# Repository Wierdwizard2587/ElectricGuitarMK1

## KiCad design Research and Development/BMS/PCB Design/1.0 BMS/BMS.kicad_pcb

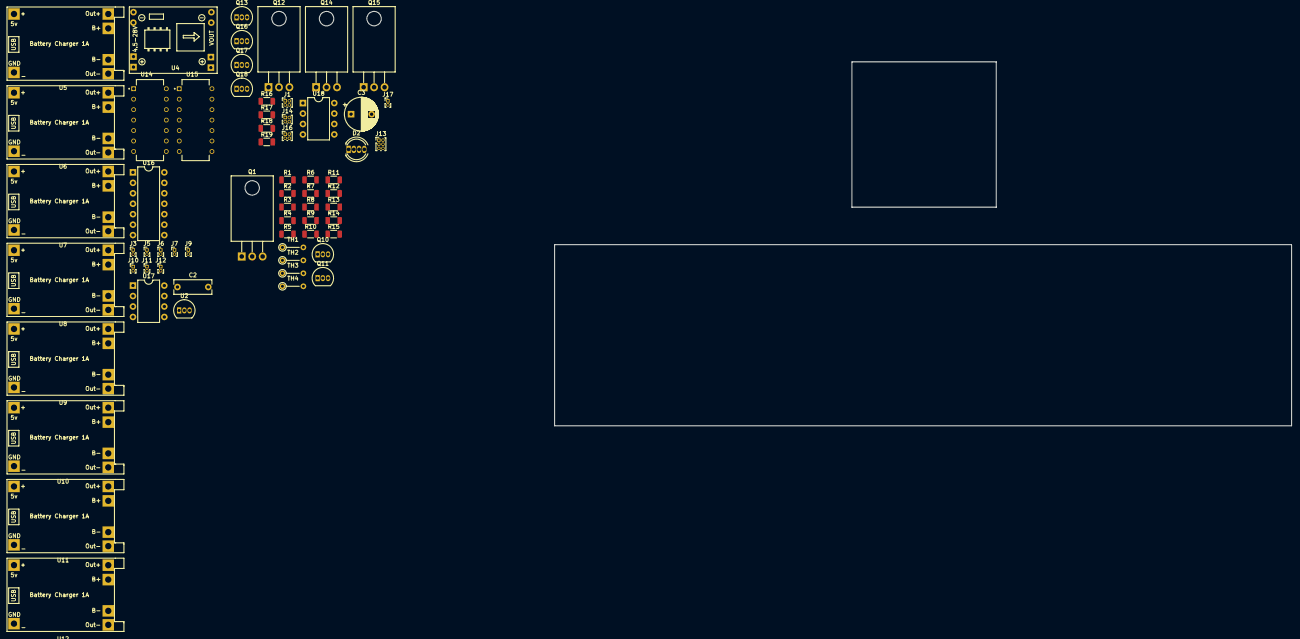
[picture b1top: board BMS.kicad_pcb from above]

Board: 2 copper layers, 179.0 x 88.4 mm, 64 parts (0 on the bottom side), 63 nets, no tracks yet.

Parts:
C2: 2nf; C_Rect_L9.0mm_W3.3mm_P7.50mm_MKT
C3: 220uf; CP_Radial_D8.0mm_P5.00mm
D2: LED_KGRB; LED_D5.0mm-4_RGB
J1, J14, J16: Conn_01x04_Pin; PinHeader_2x02_P1.00mm_Vertical
J3: Batt 1 Conn; PinHeader_1x02_P1.00mm_Vertical
J5: Batt 2 Conn; PinHeader_1x02_P1.00mm_Vertical
J6: Batt 3 Conn; PinHeader_1x02_P1.00mm_Vertical
J7: Batt 4 Conn; PinHeader_1x02_P1.00mm_Vertical
J9: Batt 5 Conn; PinHeader_1x02_P1.00mm_Vertical
J10: Batt 6 Conn; PinHeader_1x02_P1.00mm_Vertical
J11: Batt 7 Conn; PinHeader_1x02_P1.00mm_Vertical
J12: Batt 8 Conn; PinHeader_1x02_P1.00mm_Vertical
J13: Conn_01x06_Pin; PinHeader_2x03_P1.00mm_Vertical
J17: Moment ON B; PinHeader_1x02_P1.00mm_Vertical
Q1, Q12, Q14, Q15: IRL540; TO-220-3_Horizontal_TabDown
Q10, Q11, Q13, Q17, Q18: PN2222A; TO-92_Inline
Q16: ZVP2106A; TO-92_Inline
R1, R2, R3, R4, R5, R7, R11, R16: 10K; R_1206_3216Metric
R6, R8, R12, R13, R14, R15: R; R_1206_3216Metric
R9: 30K; R_1206_3216Metric
R10: 7.5K; R_1206_3216Metric
R17: 150R; R_1206_3216Metric
R18: 90R; R_1206_3216Metric
R19: 100R; R_1206_3216Metric
TH1, TH2, TH3, TH4: Thermistor_NTC; R_Axial_DIN0204_L3.6mm_D1.6mm_P5.08mm_Vertical
U2: 78L05; TO-92_Inline
U4: MP1584 Module; SRT_MPT1584EN_Module
U5, U6, U7, U8, U9, U10, U11, U12: TP4056 Charging Module; TP4056-18650
U14, U15: LM339; lm339n THT
U16: 74HC02; DIP-14_W7.62mm
U17: LM393; DIP-8_W7.62mm
U18: LMC555xN; DIP-8_W7.62mm

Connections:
BMS VCC 5V+: Q10.3 (C), R6.2, R8.2, R12.2, R16.2, TH1.2, TH2.2, TH3.2, TH4.2, U2.1 (VO), U14.3 (V+), U15.3 (V+), U16.14 (VCC), U17.8 (V+), U18.4 (R), U18.8 (VCC)
Batt Cuttoff Logic: Q1.1 (G), U17.1
Batt V: J1.2, J13.2, R9.1, R10.2, U17.3 (+)
Charge VCC: Q14.3 (S), U5.1 (IN+), U6.1 (IN+), U7.1 (IN+), U8.1 (IN+), U9.1 (IN+), U10.1 (IN+), U11.1 (IN+), U12.1 (IN+)
Charger Digital Signal: J13.4, Q12.1 (G), Q13.2 (B)
Charger In 5v+: J13.6, Q14.2 (D)
GND: C2.1, C3.2, D2.1 (K), J1.3, J13.3, J17.2, R1.1, R2.1, R3.1, R4.1, R5.1, R7.1, R10.1, R11.1, R15.2, U2.2 (GND), U4.1 (IN+), U4.4 (OUT-), U5.2 (IN-), U6.2 (IN-), U7.2 (IN-), U8.2 (IN-), U8.4 (OUT-), U9.2 (IN-), U10.2 (IN-), U11.2 (IN-), U12.2 (IN-), U12.4 (OUT-), U14.12 (V-), U15.12 (V-), U16.7 (GND), U17.4 (V-), U18.1 (GND), U18.5 (CV)
Guitar VCC 9v+: J1.4, Q12.3 (S), Q15.3 (S)
Hi T Comp Out: J1.1, R13.1, U14.1, U14.2, U14.13, U14.14, U16.2
Hi T Vref: R5.2, R6.1, U14.5 (+), U14.7 (+), U14.9 (+), U14.11 (+)
LED VCC: Q16.3 (C), Q17.3 (C), Q18.3 (C), U18.3 (Q)
Lo T Comp Out: J13.1, R14.1, U15.1, U15.2, U15.13, U15.14, U16.3
Lo T Vref: R7.2, R8.1, U15.5 (+), U15.7 (+), U15.9 (+), U15.11 (+)
unnamed: D2.4 (BA), R18.1
unnamed: D2.2 (GA), R19.1
unnamed: D2.3 (RA), R17.2
unnamed: J3.1, U5.6 (B-)
unnamed: J3.2, U5.5 (B+)
unnamed: J5.1, U6.6 (B-)
unnamed: J5.2, U6.5 (B+)
unnamed: J6.1, U7.6 (B-)
unnamed: J6.2, U7.5 (B+)
unnamed: J7.1, U8.6 (B-)
unnamed: J7.2, U8.5 (B+)
unnamed: J9.1, U9.6 (B-)
unnamed: J9.2, U9.5 (B+)
unnamed: J10.1, U10.6 (B-)
unnamed: J10.2, U10.5 (B+)
unnamed: J11.1, U11.6 (B-)
unnamed: J11.2, U11.5 (B+)
unnamed: J12.1, U12.6 (B-)
unnamed: J12.2, U12.5 (B+)
unnamed: J14.1, J16.1
unnamed: J14.2, J16.2
unnamed: J14.3, J16.3
unnamed: J14.4, J16.4
unnamed: J17.1, U18.2 (TR)
unnamed: Q10.2 (B), R13.2
unnamed: Q10.1 (E), Q11.3 (C)
unnamed: Q11.2 (B), R14.2
unnamed: Q11.1 (E), R15.1, U16.5, U16.6, U16.10
unnamed: Q13.1 (E), Q15.1 (G), Q17.2 (B), Q18.2 (B)
unnamed: Q16.1 (E), R17.1
unnamed: Q17.1 (E), R18.2
unnamed: Q18.1 (E), R19.2
unnamed: U5.4 (OUT-), U6.3 (OUT+)
unnamed: U6.4 (OUT-), U7.3 (OUT+)
unnamed: U7.4 (OUT-), U8.3 (OUT+)
unnamed: U9.4 (OUT-), U10.3 (OUT+)
unnamed: U10.4 (OUT-), U11.3 (OUT+)
unnamed: U11.4 (OUT-), U12.3 (OUT+)
unnamed: U16.1, U16.9
unnamed: R11.2, R12.1, U17.2 (-)
unnamed: R16.1, U18.7 (DIS)
unnamed: C3.1, U18.6 (THR)
Reg Batt 9v: C2.2, Q15.2 (D), U2.3 (VI), U4.3 (OUT+)
Temp 1: R1.2, TH1.1, U14.4 (-), U15.4 (-)
Temp 2: R2.2, TH2.1, U14.6 (-), U15.6 (-)
Temp 3: R3.2, TH3.1, U14.10 (-), U15.10 (-)
Temp 4: R4.2, TH4.1, U14.8 (-), U15.8 (-)
Temp Logic Output: Q13.3 (C), Q14.1 (G), Q16.2 (B), U16.4, U16.8
Unreg Batt Out: R9.2, U4.2 (IN-), U5.3 (OUT+), U9.3 (OUT+)
charger Takeover VCC 9v+: J13.5, Q12.2 (D)

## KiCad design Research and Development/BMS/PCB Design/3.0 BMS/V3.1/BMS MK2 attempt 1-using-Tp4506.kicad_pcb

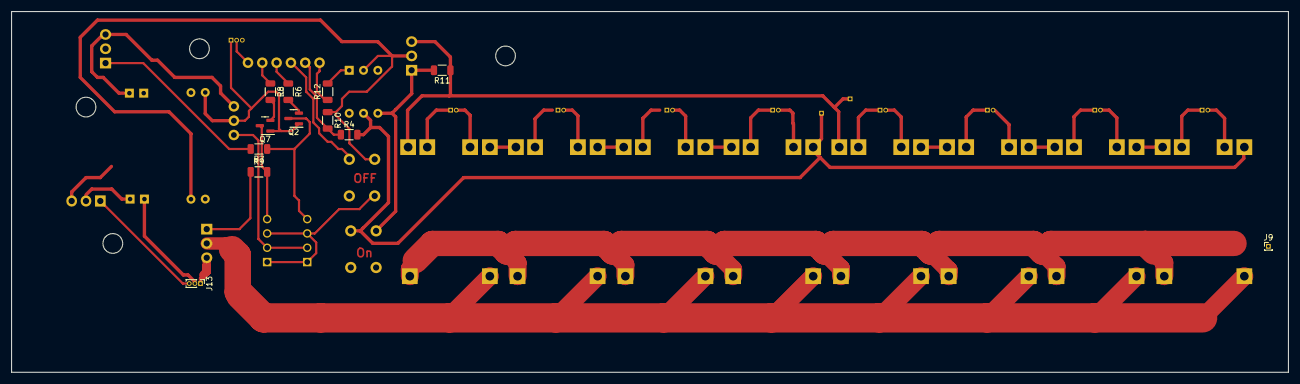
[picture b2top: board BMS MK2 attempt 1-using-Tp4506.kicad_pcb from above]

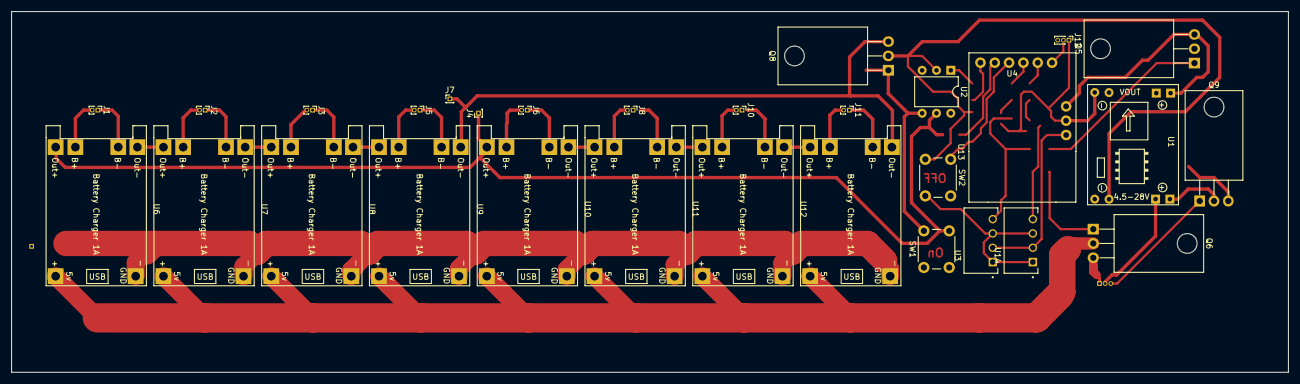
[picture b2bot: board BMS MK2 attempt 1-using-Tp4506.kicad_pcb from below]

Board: 2 copper layers, 226.6 x 64.0 mm, 42 parts (30 on the bottom side), 45 nets.

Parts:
J1: Batt 1 Conn; PinHeader_1x02_P1.00mm_Vertical
J2: Batt 2 Conn; PinHeader_1x02_P1.00mm_Vertical
J3: Batt 3 Conn; PinHeader_1x02_P1.00mm_Vertical
J4: Battery + out; PinHeader_1x01_P1.00mm_Vertical
J5: Batt 4 Conn; PinHeader_1x02_P1.00mm_Vertical
J6: Batt 5 Conn; PinHeader_1x02_P1.00mm_Vertical
J7: Battery - out; PinHeader_1x01_P1.00mm_Vertical
J8: Batt 6 Conn; PinHeader_1x02_P1.00mm_Vertical
J9: CHG GND; PinHeader_1x01_P1.00mm_Vertical
J10: Batt 7 Conn; PinHeader_1x02_P1.00mm_Vertical
J11: Batt 8 Conn; PinHeader_1x02_P1.00mm_Vertical
J12: Conn_01x03_Pin; PinHeader_1x03_P1.00mm_Vertical
J13: CHG VCCs; PinHeader_1x03_P1.00mm_Vertical
Q2, Q7: PN100; SOT-23
Q5, Q6, Q9: IRF9540N; TO-220-3_Horizontal_TabDown
Q8: IRF540N; TO-220-3_Horizontal_TabDown
R4, R7, R9, R10: 10K; R_1206_3216Metric
R6, R8: 3k3; R_1206_3216Metric
R11: 100K; R_1206_3216Metric
R12: 430R; R_1206_3216Metric
SW1, SW2: SW_SPST; SW_PUSH_6mm
U1: MP1584; SRT_MPT1584EN_Module
U2: 4N35; DIP-6_W7.62mm
U3, U14: B0515S; CONV_B0515S-1WR3
U4: ATTiny 85 Module; Digispark attiny85 board
U6, U7, U8, U9, U10, U11, U12, U13: TP4056 Charging Module; TP4056-18650

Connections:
5v attiny out: J12.3, U3.2 (Vin), U4.1 (5V), U14.2 (Vin)
15v+ CHG VCC: Q7.3 (C), R9.2, U14.4 (+Vo)
15v+ DCHG VCC: Q2.3 (C), R7.1, U3.4 (+Vo)
Batt +: J4.1, Q9.3 (S), R4.2, SW1.2 (B), U2.5, U6.3 (OUT+), U10.3 (OUT+)
Batt -: J7.1, Q8.3 (S), R11.1, U9.4 (OUT-), U13.4 (OUT-)
Batt SW VCC: R12.1, U4.9 (P5)
Battery Vref: R4.1, R10.2, U4.8 (P4)
CGE SW VCC: Q6.1 (G), R9.1
Charge VCC: Q6.2 (D), U6.1 (IN+), U7.1 (IN+), U8.1 (IN+), U9.1 (IN+), U10.1 (IN+), U11.1 (IN+), U12.1 (IN+), U13.1 (IN+)
Chgr CHG 5V+: J13.1, Q6.3 (S)
Chgr operating 12V+: J13.2, Q9.2 (D), U1.1 (IN+)
Chgr sgl 15V+: J13.3, Q9.1 (G)
DCG SW VCC: Q5.1 (G), R7.2
GND: J12.1, Q2.1 (E), Q7.1 (E), Q8.2 (D), R10.1, SW2.2 (B), U1.2 (IN-), U1.4 (OUT-), U2.2, U3.1 (GND), U3.3 (0V), U4.2 (GND), U6.2 (IN-), U7.2 (IN-), U8.2 (IN-), U9.2 (IN-), U10.2 (IN-), U11.2 (IN-), U12.2 (IN-), U13.2 (IN-), U14.1 (GND), U14.3 (0V)
unnamed: J1.1, U6.6 (B-)
unnamed: J1.2, U6.5 (B+)
unnamed: J2.1, U7.6 (B-)
unnamed: J2.2, U7.5 (B+)
unnamed: J3.1, U8.6 (B-)
unnamed: J3.2, U8.5 (B+)
unnamed: J5.1, U9.6 (B-)
unnamed: J5.2, U9.5 (B+)
unnamed: J6.1, U10.6 (B-)
unnamed: J6.2, U10.5 (B+)
unnamed: J8.1, U11.6 (B-)
unnamed: J8.2, U11.5 (B+)
unnamed: J10.1, U12.6 (B-)
unnamed: J10.2, U12.5 (B+)
unnamed: J11.1, U13.6 (B-)
unnamed: J11.2, U13.5 (B+)
unnamed: J12.2, U4.4 (P0)
unnamed: Q2.2 (B), R6.2
unnamed: Q7.2 (B), R8.2
unnamed: Q8.1 (G), R11.2, SW1.1 (A), U2.4
unnamed: R12.2, U2.1
unnamed: SW2.1 (A), U4.7 (P3)
unnamed: R8.1, U4.5 (P1)
unnamed: R6.1, U4.6 (P2)
unnamed: U6.4 (OUT-), U7.3 (OUT+)
unnamed: U7.4 (OUT-), U8.3 (OUT+)
unnamed: U8.4 (OUT-), U9.3 (OUT+)
unnamed: U10.4 (OUT-), U11.3 (OUT+)
unnamed: U11.4 (OUT-), U12.3 (OUT+)
unnamed: U12.4 (OUT-), U13.3 (OUT+)
Reg Batt 9v: Q5.3 (S), U1.3 (OUT+), U4.3 (VIN)

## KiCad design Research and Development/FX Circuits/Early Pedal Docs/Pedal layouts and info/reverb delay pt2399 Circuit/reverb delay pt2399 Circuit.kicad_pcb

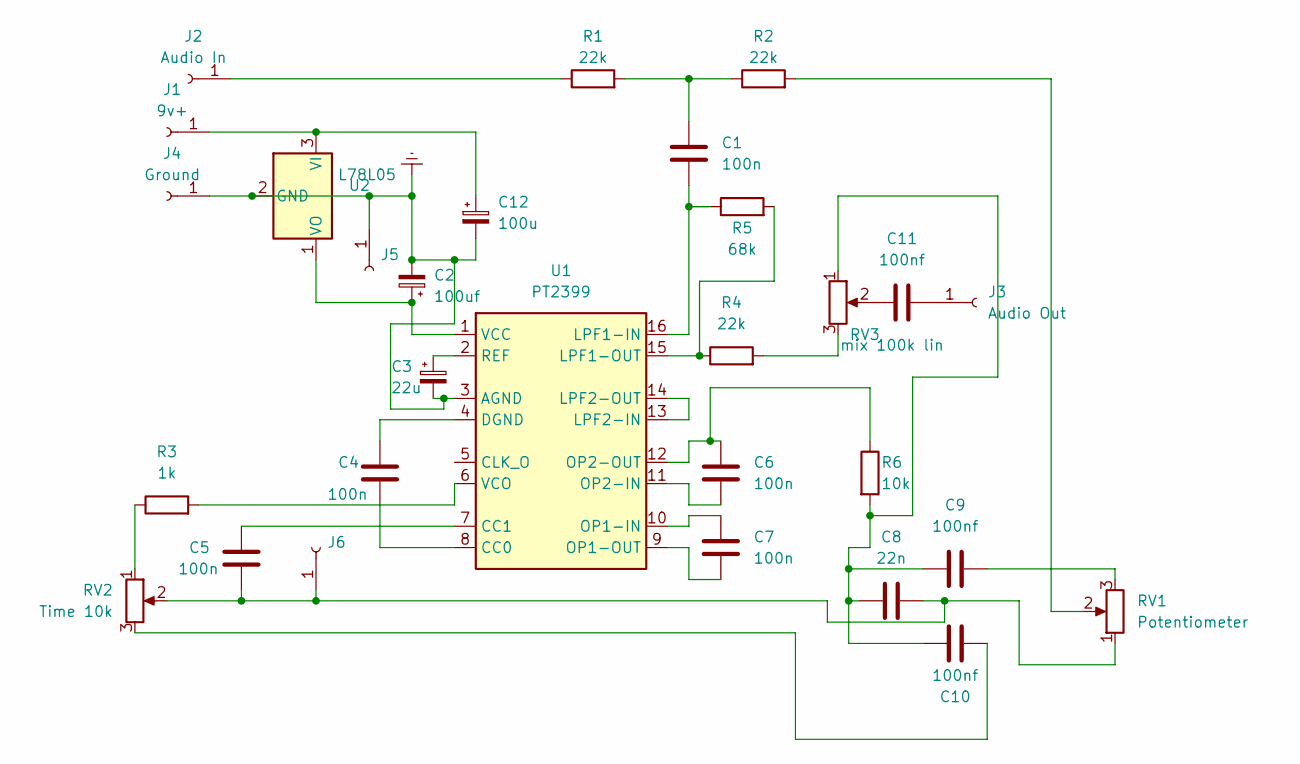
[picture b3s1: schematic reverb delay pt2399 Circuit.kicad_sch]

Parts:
C1, C4, C5: 100n; C_Rect_L9.0mm_W2.7mm_P7.50mm_MKT
C2: 100uf; CP_Radial_D5.0mm_P2.00mm
C3: 22u; CP_Radial_D5.0mm_P2.00mm
C6, C7: 100n; C_Disc_D5.0mm_W2.5mm_P2.50mm
C8: 22n; C_Disc_D3.0mm_W2.0mm_P2.50mm
C9, C10, C11: 100nf; C_Rect_L9.0mm_W2.7mm_P7.50mm_MKT
C12: 100u; CP_Radial_D5.0mm_P2.00mm
J1: 9v+; PinHeader_1x01_P1.00mm_Vertical
J2: Audio In; PinHeader_1x01_P1.00mm_Vertical
J3: Audio Out; PinHeader_1x01_P1.00mm_Vertical
J4: Ground; PinHeader_1x01_P1.00mm_Vertical
J5: jumper1 start; PinHeader_1x01_P1.00mm_Vertical
J6: jumper1 end; PinHeader_1x01_P1.00mm_Vertical
R1, R2: 22k; R_Axial_DIN0204_L3.6mm_D1.6mm_P7.62mm_Horizontal
R3: 1k; R_Axial_DIN0204_L3.6mm_D1.6mm_P5.08mm_Horizontal
R4: 22k; R_Axial_DIN0204_L3.6mm_D1.6mm_P5.08mm_Horizontal
R5: 68k; R_Axial_DIN0204_L3.6mm_D1.6mm_P5.08mm_Horizontal
R6: 10k; R_Axial_DIN0204_L3.6mm_D1.6mm_P5.08mm_Horizontal
RV1: Potentiometer; Potentiometer_Bourns_3386C_Horizontal
RV2: Time 10k; Potentiometer_Bourns_3386C_Horizontal
RV3: mix 100k lin; Potentiometer_Bourns_3386C_Horizontal
U1: PT2399; DIP-16_W7.62mm_Socket
U2: L78L05; TO-92_Inline

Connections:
unnamed: C1.1, R1.2, R2.1
unnamed: C9.2, RV1.3
unnamed: C8.1, C9.1, C10.1, R6.2, RV3.1
unnamed: C10.2, RV2.3
unnamed: C11.1, RV3.2
unnamed: C12.1, J1.1, U2.3 (VI)
unnamed: J2.1, R1.1
unnamed: C11.2, J3.1
unnamed: C5.2, C8.2, J6.1, RV1.1, RV2.2
unnamed: R2.2, RV1.2
unnamed: R3.1, RV2.1
unnamed: R4.2, RV3.3
unnamed: C4.1, U1.8 (CC0)
unnamed: C5.1, U1.7 (CC1)
unnamed: C1.2, R5.1, U1.16 (LPF1-IN)
unnamed: R4.1, R5.2, U1.15 (LPF1-OUT)
unnamed: U1.13 (LPF2-IN), U1.14 (LPF2-OUT)
unnamed: C7.1, U1.10 (OP1-IN)
unnamed: C7.2, U1.9 (OP1-OUT)
unnamed: C6.2, U1.11 (OP2-IN)
unnamed: C6.1, R6.1, U1.12 (OP2-OUT)
unnamed: C3.1, U1.2 (REF)
unnamed: C2.1, U1.1 (VCC), U2.1 (VO)
unnamed: R3.2, U1.6 (VCO)

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
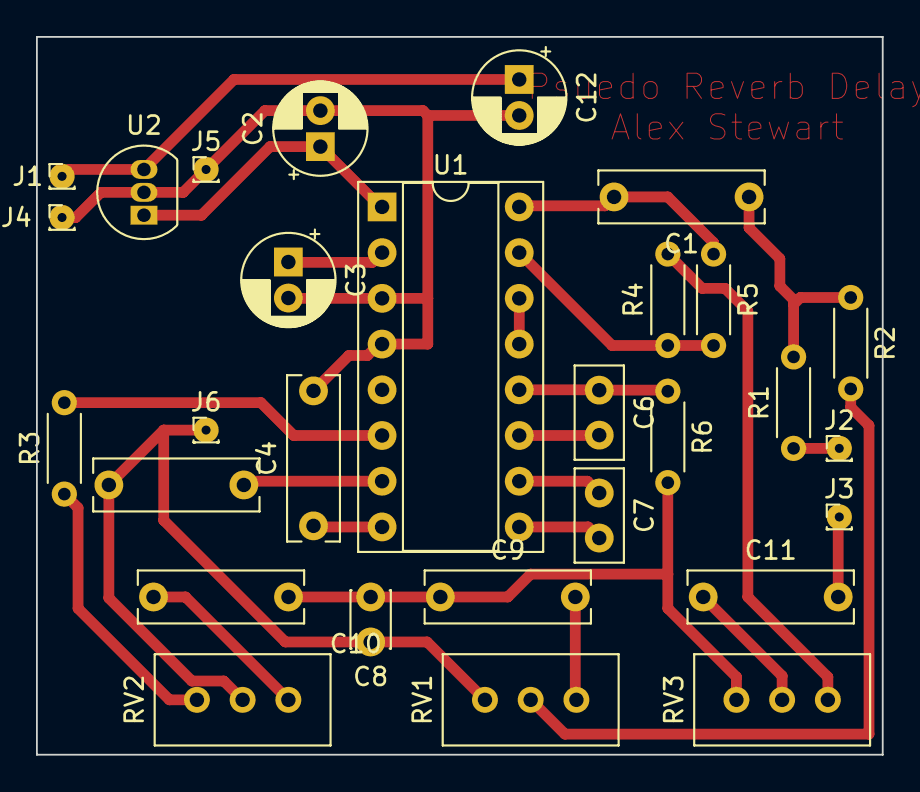
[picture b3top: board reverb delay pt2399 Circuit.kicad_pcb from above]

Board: 2 copper layers, 47.0 x 39.9 mm, 29 parts (0 on the bottom side), 25 nets.

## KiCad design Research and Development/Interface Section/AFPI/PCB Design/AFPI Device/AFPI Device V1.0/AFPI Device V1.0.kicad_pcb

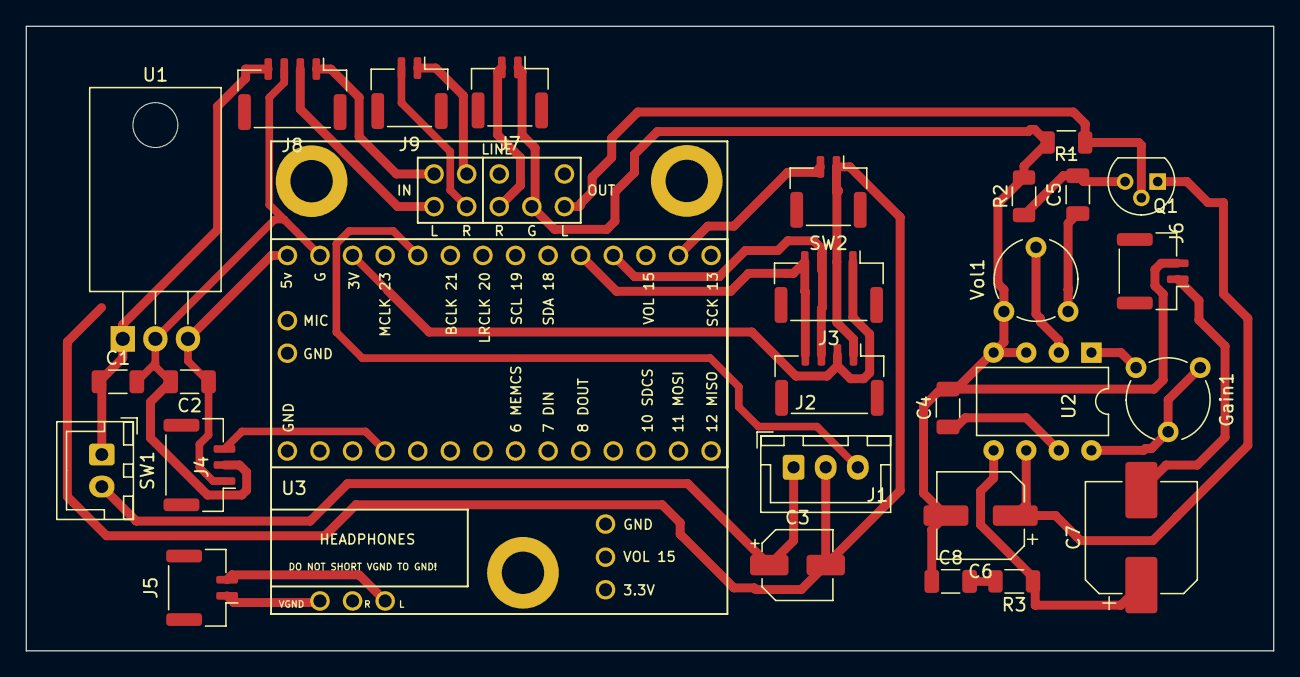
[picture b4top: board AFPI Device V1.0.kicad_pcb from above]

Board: 2 copper layers, 97.2 x 48.7 mm, 28 parts (0 on the bottom side), 28 nets.

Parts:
C1: 330nf; C_1206_3216Metric
C2: 100nf; C_1206_3216Metric
C3: 10uf 35V; CP_Elec_5x5.4
C4: 100n; C_1206_3216Metric
C5, C8: 47n; C_1206_3216Metric
C6: 100u; CP_Elec_6.3x7.7
C7: 220u; CP_Elec_8x10.5
Gain1: 1kB; Potentiometer_Piher_PT-6-V_Vertical
J1: Batt In; JST_XH_B3B-XH-A_1x03_P2.50mm_Vertical
J2: OLED Screen; JST_GH_BM04B-GHS-TBT_1x04-1MP_P1.25mm_Vertical
J3: Quad Rotary Encoder Board; JST_GH_BM04B-GHS-TBT_1x04-1MP_P1.25mm_Vertical
J4: RGB LEDs; JST_GH_BM03B-GHS-TBT_1x03-1MP_P1.25mm_Vertical
J5: Headphone Out; JST_GH_BM02B-GHS-TBT_1x02-1MP_P1.25mm_Vertical
J6: Speaker Output; JST_GH_BM02B-GHS-TBT_1x02-1MP_P1.25mm_Vertical
J7: Aux Out; JST_GH_BM02B-GHS-TBT_1x02-1MP_P1.25mm_Vertical
J8: Guitar Line/Pickup V; JST_GH_BM04B-GHS-TBT_1x04-1MP_P1.25mm_Vertical
J9: Backing Track Input; JST_GH_BM02B-GHS-TBT_1x02-1MP_P1.25mm_Vertical
Q1: MPF102; TO-92
R1: 1M5; R_1206_3216Metric
R2: 3k9; R_1206_3216Metric
R3: 10R; R_1206_3216Metric
SW1: Main Power SW; JST_XH_B2B-XH-A_1x02_P2.50mm_Vertical
SW2: Home Button SW; JST_GH_BM02B-GHS-TBT_1x02-1MP_P1.25mm_Vertical
U1: L7805; TO-220-3_Horizontal_TabDown
U2: LM386; DIP-8_W7.62mm
U3: Teensy4.0_AudioShield_REVD; Teensy 4.0 audioshield
Vol1: 10kB; Potentiometer_Piher_PT-6-V_Vertical

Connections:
+3.3V: J2.2, J3.1, U3.28 (3V)
+5V: C2.1, J4.1, U1.3 (OUT), U3.30 (5V)
+9V: C1.1, C6.1, J8.4, Q1.1 (D), SW1.1 (A), U1.1 (IN), U2.6 (V+)
Batt Vref: J1.3, U3.26 (22_A8_CTX1)
GND: C1.2, C2.2, C3.2, J1.2, J2.1, J3.2, J4.2, J8.3, SW2.1 (A), U1.2 (GND), U3.1 (GND), U3.29 (GND)
GND1: C4.2, C6.2, C8.1, J6.2, J7.1, R1.2, R2.2, U2.3 (+), U2.4 (GND), U3.32 (LINE_OUT_GND), Vol1.3
HP Line: J5.2, U3.41 (HEADPHONES_L)
HP VGND: J5.1, U3.43 (HEADPHONES_VGND)
Line OUT R: J7.2, U3.33 (LINE_OUT_R)
Line in R: J9.2, U3.34 (LINE_IN_R)
Line in R GND: J9.1, U3.36 (LINE_IN_R_GND)
unnamed: C5.1, Vol1.1
unnamed: C7.1, R3.1, U2.5
unnamed: C8.2, R3.2
unnamed: Gain1.1, U2.1 (GAIN)
unnamed: Gain1.2, Gain1.3, U2.8 (GAIN)
unnamed: C3.1, J1.1, SW1.2 (B)
unnamed: C7.2, J6.1
unnamed: J8.1, U3.37 (LINE_IN_L_GND)
unnamed: J8.2, U3.35 (LINE_IN_L)
unnamed: Q1.2 (G), R1.1, U3.31 (LINE_OUT_L)
unnamed: C5.2, Q1.3 (S), R2.1
unnamed: SW2.2 (B), U3.18 (14_A0_TX3_SPDIF_OUT)
unnamed: U2.2 (-), Vol1.2
unnamed: C4.1, U2.7 (BYPASS)
Pin 2: J4.3, U3.4 (2_OUT2)
Pin 16 SCL1: J2.3, J3.3, U3.20 (16_A2_RX4_SCL1)
Pin 17 SDA1: J2.4, J3.4, U3.21 (17_A3_TX4_SDA1)

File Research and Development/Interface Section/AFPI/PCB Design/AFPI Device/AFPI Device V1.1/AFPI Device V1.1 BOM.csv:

"Id";"Designator";"Footprint";"Quantity";"Designation";"Supplier and ref";
1;"C1";"C_1206_3216Metric";1;"330nf";;;
2;"C5,C8";"C_1206_3216Metric";2;"47n";;;
3;"C2";"C_1206_3216Metric";1;"100nf";;;
4;"Gain1";"Potentiometer_Piher_PT-6-V_Vertical";1;"1kB";;;
5;"SW1";"JST_XH_B2B-XH-A_1x02_P2.50mm_Vertical";1;"MAIN SW";;;
6;"J2";"JST 1.25mm THT 01x04";1;"OLED";;;
7;"Vol1";"Potentiometer_Piher_PT-6-V_Vertical";1;"10kB";;;
8;"R1";"R_1206_3216Metric";1;"1M5";;;
9;"C6";"CP_Elec_6.3x7.7";1;"100u";;;
10;"J3";"JST 1.25mm THT 01x04";1;"ROT ENC ";;;
11;"C3";"CP_Elec_5x5.4";1;"10uf 35V";;;
12;"U1";"SOT-223";1;"L7805";;;
13;"C7";"CP_Elec_8x10.5";1;"220u";;;
14;"R2";"R_1206_3216Metric";1;"3k9";;;
15;"R3";"R_1206_3216Metric";1;"10R";;;
16;"SW2";"JST 1.25mm THT 01x02";1;"Home SW";;;
17;"U3";"Teensy 4.0 audioshield";1;"Teensy4.0_AudioShield_REVD";;;
18;"U2";"DIP-8_W7.62mm";1;"LM386";;;
19;"C4";"C_1206_3216Metric";1;"100n";;;
20;"Q1";"TO-92";1;"MPF102";;;
21;"J9";"JST 1.25mm THT 01x02";1;"BACK I";;;
22;"J6";"JST 1.25mm THT 01x02";1;"SP O";;;
23;"J1";"JST_XH_B3B-XH-A_1x03_P2.50mm_Vertical";1;"Batt I";;;
24;"J5";"JST 1.25mm THT 01x02";1;"HP O";;;
25;"J8";"JST 1.25mm THT 01x04";1;"LINE I/PKP V";;;
26;"J7";"JST 1.25mm THT 01x02";1;"AU O";;;
27;"J4";"JST 1.25mm THT 01x03";1;"RGB O";;;

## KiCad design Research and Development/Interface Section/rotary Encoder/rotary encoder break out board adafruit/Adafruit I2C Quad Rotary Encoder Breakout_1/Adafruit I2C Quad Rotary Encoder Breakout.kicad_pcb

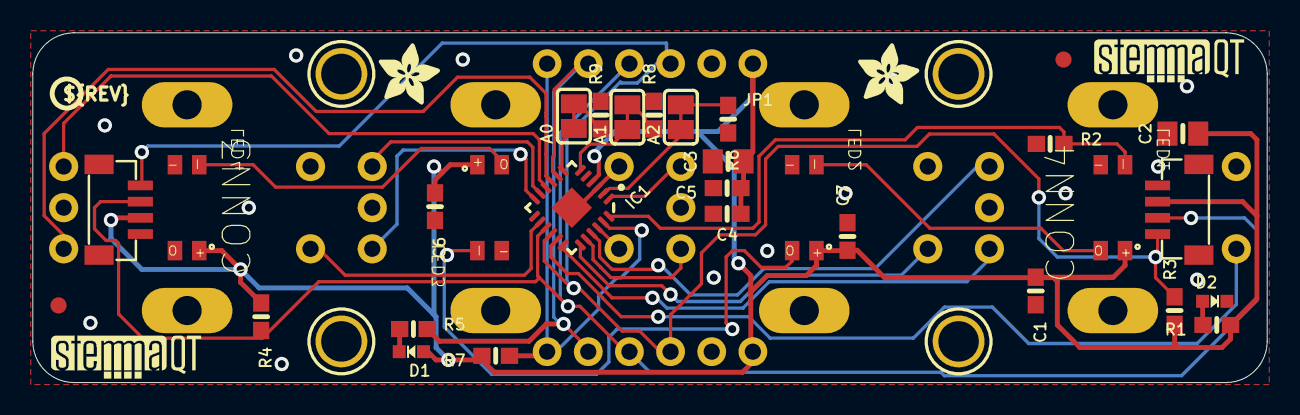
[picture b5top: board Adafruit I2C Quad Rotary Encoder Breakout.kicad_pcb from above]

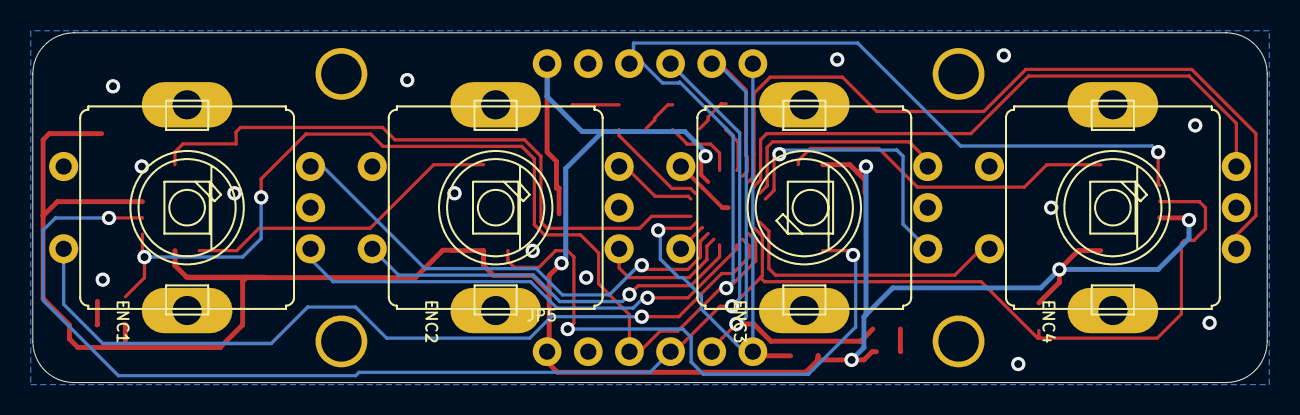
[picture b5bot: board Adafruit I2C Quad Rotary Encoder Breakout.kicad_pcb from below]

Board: 2 copper layers, 76.2 x 21.6 mm, 78 parts (25 on the bottom side), 30 nets.

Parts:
A0, A1, A2: SOLDERJUMPER_CLOSEDWIRE
C1, C5, C6, C7: 1uF; 0603-NO
C2, C3: 10uF; 0805-NO
C4: 0.1uF; 0603-NO
CONN3, CONN4: STEMMA_I2C_QTRA; JST_SH4_RA
D1: RED; CHIPLED_0603_NOOUTLINE
D2: GREEN; CHIPLED_0603_NOOUTLINE
ENC1, ENC2, ENC3, ENC4: PEC11+SWITCH
FID1, FID2: FIDUCIAL_1MM
IC1: ATTINY8X7-MU; QFN24_4MM
JP1, JP5: 1X06_ROUND_70
LED1, LED2, LED3, LED4: WS2812B_SK6812E; NEO3535_REVERSE
PLABEL0: PLABEL0
PLABEL1: PLABEL1
PLABEL2: PLABEL2
PLABEL3: PLABEL3
PLABEL4: PLABEL4
PLABEL5: PLABEL5
PLABEL6: PLABEL6
PLABEL7: PLABEL7
PLABEL8: PLABEL8
PLABEL9: PLABEL9
PLABEL10: PLABEL10
PLABEL11: PLABEL11
PLABEL12: PLABEL12
PLABEL13: PLABEL13
PLABEL14: PLABEL14
PLABEL15: PLABEL15
PLABEL16: PLABEL16
PLABEL17: PLABEL17
PLABEL18: PLABEL18
PLABEL19: PLABEL19
PLABEL20: PLABEL20
PLABEL21: PLABEL21
PLABEL22: PLABEL22
PLABEL23: PLABEL23
PLABEL24: PLABEL24
PLABEL25: PLABEL25
PLABEL26: PLABEL26
PLABEL27: PLABEL27
PLABEL28: PLABEL28
PLABEL29: PLABEL29
PLABEL30: PLABEL30
PLABEL31: PLABEL31
PLABEL32: PLABEL32
R1, R2, R3, R4, R5, R6, R7, R8, R9: 10K; 0603-NO
U$2, U$9: ADAFRUIT_3.5MM
U$3, U$17, U$19, U$21: MOUNTINGHOLE2.5; MOUNTINGHOLE_2.5_PLATED
U$25: PCBFEAT-REV-040
U$30, U$31: STEMMAQT

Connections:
ADDR0: A0.1, IC1.7
ADDR1: A1.1, IC1.6
ADDR2: A2.1, IC1.2
GND: C1.2, C2.2, C3.2, C4.2, C5.2, C6.2, C7.2, CONN3.1, CONN3.MT1, CONN3.MT2, CONN4.1, CONN4.MT1, CONN4.MT2, D2.C, ENC1.P$2, ENC1.P$C, ENC1.P$GND1, ENC1.P$GND2, ENC2.P$2, ENC2.P$C, ENC2.P$GND1, ENC2.P$GND2, ENC3.P$2, ENC3.P$C, ENC3.P$GND1, ENC3.P$GND2, ENC4.P$2, ENC4.P$C, ENC4.P$GND1, ENC4.P$GND2, IC1.3, IC1.THERM, JP1.2, JP5.2, LED1.3-GND, LED2.3-GND, LED3.3-GND, LED4.3-GND, R2.1, R6.2, R8.2, R9.2
INT: IC1.8, JP1.5, JP5.5, R5.2
unnamed: D2.A, R1.2
unnamed: LED1.2-DOUT, LED2.4-DIN
unnamed: LED2.2-DOUT, LED3.4-DIN
unnamed: LED3.2-DOUT, LED4.4-DIN
unnamed: D1.C, R5.1
unnamed: A2.2, R6.1
unnamed: A1.2, R8.1
unnamed: A0.2, R9.1
NEO_IN: IC1.24, LED1.4-DIN, R2.2
ROT0_A: ENC1.P$A, IC1.18
ROT0_B: ENC1.P$B, IC1.21
ROT0_SW: ENC1.P$1, IC1.17
ROT1_A: ENC2.P$A, IC1.20
ROT1_B: ENC2.P$B, IC1.1
ROT1_SW: ENC2.P$1, IC1.19
ROT2_A: ENC3.P$A, IC1.12
ROT2_B: ENC3.P$B, IC1.11
ROT2_SW: ENC3.P$1, IC1.22
ROT3_A: ENC4.P$A, IC1.9
ROT3_B: ENC4.P$B, IC1.10
ROT3_SW: ENC4.P$1, IC1.14
SCL: CONN3.4, CONN4.4, IC1.16, JP1.3, JP5.3, R3.2
SDA: CONN3.3, CONN4.3, IC1.15, JP1.4, JP5.4, R4.2
UPDI: IC1.23, JP1.6, JP5.6, R7.1
VCC: C1.1, C2.1, C3.1, C4.1, C5.1, C6.1, C7.1, CONN3.2, CONN4.2, D1.A, IC1.4, JP1.1, JP5.1, LED1.1-VDD, LED2.1-VDD, LED3.1-VDD, LED4.1-VDD, R1.1, R3.1, R4.1, R7.2
